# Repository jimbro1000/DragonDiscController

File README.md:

# Dragon 32/64 Disk Controller Card #

This project contains the design and build
documents for a recreation of the DragonDos
disc controller

## Design ##

The schematics use a WDC WD2797 disc controller
IC as the core of the board, this is consistent
with the original DragonData design. Other 
2797 ICs from different manufacturers should
still work

Other than the rom and controller the discrete
logic chips are surface mount to help with the
availability of components. In all cases the
surface mount parts are of the largest versions
available to try and make the assembly of the
board feasible for hand soldering

## Progress ##

In the current state the board is untested

The PCB layout is (very) generous on dimensions
and needs work to shrink it down. Iterating on
this won't change the functionality and should
significantly reduce the size of the board, and
hence the cost of fabrication

## Assembly and BoM ##

Until the board progresses to a point where it
can be tested the assembly instructions and the
proven bill of materials are left unpublished

## Calibration ##

1. Adjust the RPW timing - measure the pulse
width of the TG43 signal from pin 29 on U2. 
Use R10 to fix the pulse at 600ns

2. Adjust the WPW timing - measure the pulse
width of the signal from pin 3 of U6, pin 31 of U2,
or pin 22 of the IDC connector (the IDC pin is
inverted). Use R9 to fix the pulse at 300ns

3. Adjust VC0 timing - measure the frequency
of the DIRC signal from pin 1 of U6, pin 16 of U2,
or pin 18 of the IDC connector (the IDC pin is
inverted). Use C3 to set the signal at 250KHz

### Complete Adjustment Procedure ###

The official documentation identifies a more
complex and thorough adjustment procedure.
Where !TEST is referenced you can use the test
point on the board at J1. Pin 1 is connected to
!TEST on U2 (pin 22)

#### Write Precompensation ####

1. Set !TEST to high (1)
2. Strobe !MR on U2 Pin 19
3. Set !TEST to low (0)
4. Measure pulse width on U2 Pin 31
5. Adjust R9 until pulse width is 300ns
6. Set !TEST to high (1)

#### Data Separator ####

1. Set !Test to high (1)
2. Strobe !MR on U2 pin 19
3. Check that !5/8 and !DDEN are set properly. U2 pin 17 and 37
4. Set !TEST to low (0)
5. Measure pulse width on U2 Pin 29
6. Adjust R10 until pulse width is 600ns
7. Measure frequency on U2 pin 16
8. Adjust C3 until frequency is 250KHz
9. Set !TEST to high (1)

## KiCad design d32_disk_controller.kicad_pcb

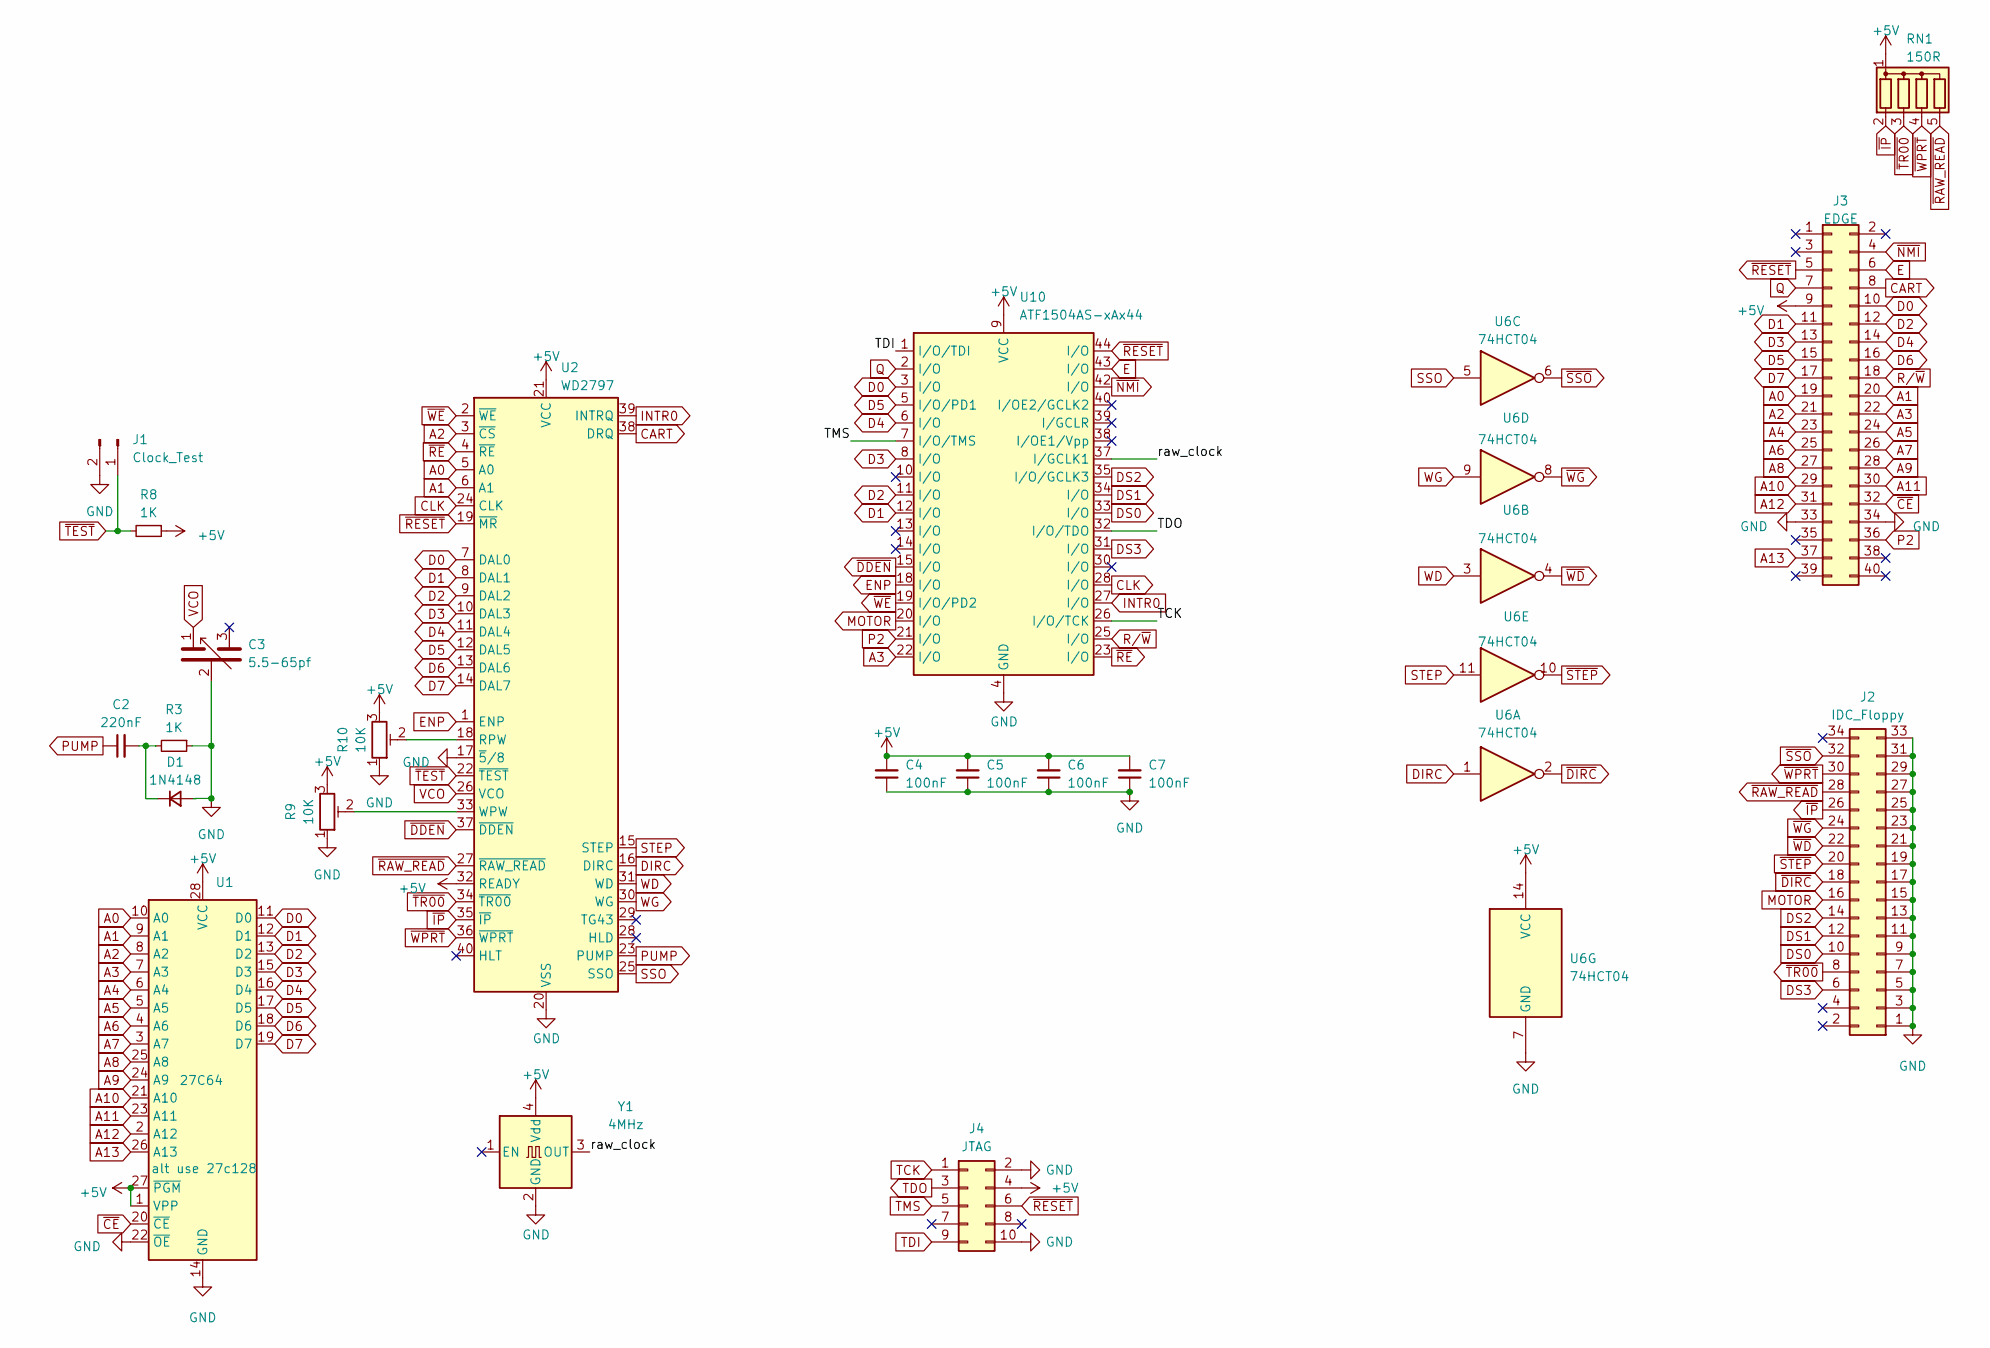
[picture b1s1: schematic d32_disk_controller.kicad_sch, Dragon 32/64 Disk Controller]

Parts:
C2: 220nF; C_0805_2012Metric_Pad1.18x1.45mm_HandSolder
C3: 5.5-65pf; Trimmer-10mm
C4, C5, C6, C7: 100nF; C_0402_1005Metric
D1: 1N4148; D_0805_2012Metric_Pad1.15x1.40mm_HandSolder
J1: Clock_Test; TestPoint_2Pads_Pitch2.54mm_Drill0.8mm
J2: IDC_Floppy; IDC-Header_2x17_P2.54mm_Latch_Horizontal
J3: EDGE; D32_Edge
J4: JTAG; PinHeader_2x05_P2.54mm_Vertical
R3, R8: 1K; R_0805_2012Metric_Pad1.20x1.40mm_HandSolder
R9, R10: 10K; Potentiometer_Bourns_3296Y_Vertical
RN1: 150R; R_Array_SIP5
U1: 27C64; DIP-28_W15.24mm
U2: WD2797; DIP-40_W15.24mm
U6: 74HCT04; SOIC-14_3.9x8.7mm_P1.27mm; DigiKey 296-1205-1-ND
U10: ATF1504AS-xAx44; TQFP-44_10x10mm_P0.8mm
Y1: 4MHz; Oscillator_SMD_Abracon_ASV-4Pin_7.0x5.1mm

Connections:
+5V: C4.2, C5.2, C6.2, C7.2, J3.9, J4.4, R8.1, R9.3, R10.3, RN1.1 (common), U1.1 (VPP), U1.27 (~PGM), U1.28 (VCC), U2.21 (VCC), U2.32 (READY), U6.14 (VCC), U10.9 (VCC), U10.17 (VCC), U10.29 (VCC), U10.41 (VCC), Y1.4 (Vdd)
/raw_clock: U10.37 (I/GCLK1), Y1.3 (OUT)
A0: J3.19, U1.10 (A0), U2.5 (A0)
A1: J3.20, U1.9 (A1), U2.6 (A1)
A2: J3.21, U1.8 (A2), U2.3 (~CS)
A3: J3.22, U1.7 (A3), U10.22 (I/O)
A4: J3.23, U1.6 (A4)
A5: J3.24, U1.5 (A5)
A6: J3.25, U1.4 (A6)
A7: J3.26, U1.3 (A7)
A8: J3.27, U1.25 (A8)
A9: J3.28, U1.24 (A9)
A10: J3.29, U1.21 (A10)
A11: J3.30, U1.23 (A11)
A12: J3.31, U1.2 (A12)
A13: J3.37, U1.26 (A13)
CART: J3.8, U2.38 (DRQ)
CLK: U2.24 (CLK), U10.28 (I/O)
D0: J3.10, U1.11 (D0), U2.7 (DAL0), U10.3 (I/O)
D1: J3.11, U1.12 (D1), U2.8 (DAL1), U10.12 (I/O)
D2: J3.12, U1.13 (D2), U2.9 (DAL2), U10.11 (I/O)
D3: J3.13, U1.15 (D3), U2.10 (DAL3), U10.8 (I/O)
D4: J3.14, U1.16 (D4), U2.11 (DAL4), U10.6 (I/O)
D5: J3.15, U1.17 (D5), U2.12 (DAL5), U10.5 (I/O/PD1)
D6: J3.16, U1.18 (D6), U2.13 (DAL6)
D7: J3.17, U1.19 (D7), U2.14 (DAL7)
DIRC: U2.16 (DIRC), U6.1
DS0: J2.10, U10.33 (I/O)
DS1: J2.12, U10.34 (I/O)
DS2: J2.14, U10.35 (I/O/GCLK3)
DS3: J2.6, U10.31 (I/O)
E: J3.6, U10.43 (I/O)
ENP: U2.1 (ENP), U10.18 (I/O)
GND: C3.2, C4.1, C5.1, C6.1, C7.1, D1.2 (A), J1.2, J2.1, J2.3, J2.5, J2.7, J2.9, J2.11, J2.13, J2.15, J2.17, J2.19, J2.21, J2.23, J2.25, J2.27, J2.29, J2.31, J2.33, J3.33, J3.34, J4.2, J4.10, R3.1, R9.1, R10.1, U1.14 (GND), U1.22 (~OE), U2.17 (~5/8), U2.20 (VSS), U6.7 (GND), U10.4 (GND), U10.16 (GND), U10.24 (GND), U10.36 (GND), Y1.2 (GND)
INTR0: U2.39 (INTRQ), U10.27 (I/O)
MOTOR: J2.16, U10.20 (I/O)
unnamed: C2.2, D1.1 (K), R3.2
unnamed: R10.2, U2.18 (RPW)
unnamed: R9.2, U2.33 (WPW)
P2: J3.36, U10.21 (I/O)
PUMP: C2.1, U2.23 (PUMP)
Q: J3.7, U10.2 (I/O)
R/~W: J3.18, U10.25 (I/O)
SSO: U2.25 (SSO), U6.5
STEP: U2.15 (STEP), U6.11
TCK: J4.1, U10.26 (I/O/TCK)
TDI: J4.9, U10.1 (I/O/TDI)
TDO: J4.3, U10.32 (I/O/TDO)
TMS: J4.5, U10.7 (I/O/TMS)
VCO: C3.1, U2.26 (VCO)
WD: U2.31 (WD), U6.3
WG: U2.30 (WG), U6.9
~CE: J3.32, U1.20 (~CE)
~DDEN: U2.37 (~DDEN), U10.15 (I/O)
~DIRC: J2.18, U6.2
~IP: J2.26, RN1.2 (R1), U2.35 (~IP)
~NMI: J3.4, U10.42 (I/O)
~RAW_READ: J2.28, RN1.5 (R4), U2.27 (~RAW_READ)
~RESET: J3.5, J4.6, U2.19 (~MR), U10.44 (I/O)
~RE: U2.4 (~RE), U10.23 (I/O)
~SSO: J2.32, U6.6
~STEP: J2.20, U6.10
~TEST: J1.1, R8.2, U2.22 (~TEST)
~TR00: J2.8, RN1.3 (R2), U2.34 (~TR00)
~WD: J2.22, U6.4
~WE: U2.2 (~WE), U10.19 (I/O/PD2)
~WG: J2.24, U6.8
~WPRT: J2.30, RN1.4 (R3), U2.36 (~WPRT)

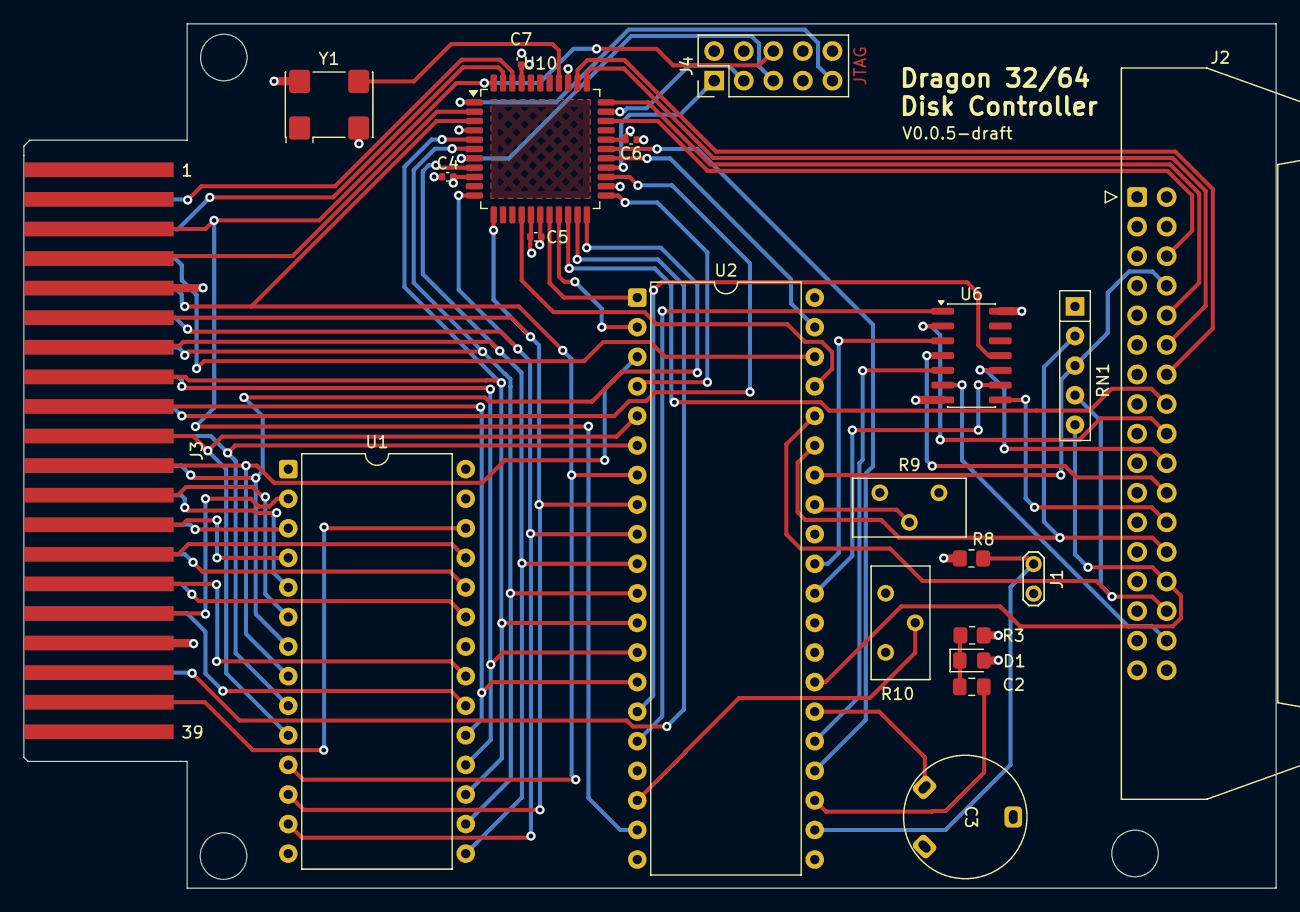
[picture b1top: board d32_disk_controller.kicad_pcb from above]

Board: 4 copper layers, 107.5 x 74.2 mm, 21 parts (0 on the bottom side), 68 nets.

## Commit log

2023-07-05 redraft traces
2023-07-05 rework traces
2023-07-06 revise tracing
2023-07-06 add render to readme
2023-07-06 verify component availability
2023-07-06 update version
2023-07-21 revise board for better component selection
2023-07-21 update render
2023-07-21 update from component selection change
2023-07-21 add test points
2026-03-23 prepare for cpld
2026-03-23 convert to small CPLD
2026-03-23 add CPLD bin files
2026-03-23 change CPLD to smallest size
